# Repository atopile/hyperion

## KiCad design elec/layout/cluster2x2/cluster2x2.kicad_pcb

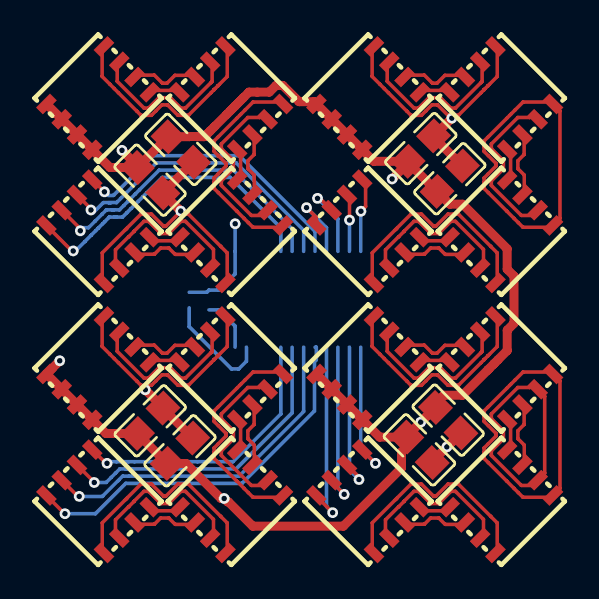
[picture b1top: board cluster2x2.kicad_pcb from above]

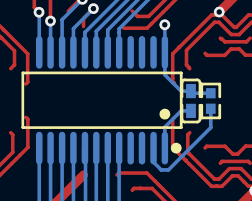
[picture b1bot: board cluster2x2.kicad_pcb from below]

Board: 2 copper layers, 31 parts (3 on the bottom side), 69 nets.

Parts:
C1, C2, C3, C4, C5, C6, C7, C8: 10µF ±10% 25V X5R; C0805
C9: 100nF ±10% 16V X7R; C0402
LED1, LED2, LED3, LED4, LED5, LED6, LED7, LED8, LED9, LED10, LED11, LED12, LED13, LED14, LED15, LED16: LED-SMD_8P-L5.0-W5.0-P1.20_HL-5050RGBW-S1-A27
R1: 309Ω ±1% 62.5mW; R0402
U1: SSOP-24_L8.8-W4.0-P0.64-LS6.2-BL
U2, U3, U4, U5: pixel15

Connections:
REXT: R1.1, U1.23
power-GND: C9.2, R1.2, U1.1
power-VCC: C9.1, U1.24
power_shim-GND: C1.2, C2.2, C3.2, C4.2, C5.2, C6.2, C7.2, C8.2
power_shim-VCC: C1.1, C2.1, C3.1, C4.1, C5.1, C6.1, C7.1, C8.1, LED1.2, LED1.4, LED1.6, LED1.8, LED5.2, LED5.4, LED5.6, LED5.8, LED9.2, LED9.4, LED9.6, LED9.8, LED13.2, LED13.4, LED13.6, LED13.8
rgbs[1]-anodes-anode-0: LED1.3, LED2.4
rgbs[1]-anodes-anode-1: LED1.1, LED2.2
rgbs[1]-anodes-anode-2: LED1.5, LED2.6
rgbs[1]-anodes-anode-3: LED1.7, LED2.8
rgbs[1]-anodes-anode-4: LED5.3, LED6.4
rgbs[1]-anodes-anode-5: LED5.1, LED6.2
rgbs[1]-anodes-anode-6: LED5.5, LED6.6
rgbs[1]-anodes-anode-7: LED5.7, LED6.8
rgbs[1]-anodes-anode-8: LED9.3, LED10.4
rgbs[1]-anodes-anode-9: LED9.1, LED10.2
rgbs[1]-anodes-anode-10: LED9.5, LED10.6
rgbs[1]-anodes-anode-11: LED9.7, LED10.8
rgbs[1]-anodes-anode-12: LED13.3, LED14.4
rgbs[1]-anodes-anode-13: LED13.1, LED14.2
rgbs[1]-anodes-anode-14: LED13.5, LED14.6
rgbs[1]-anodes-anode-15: LED13.7, LED14.8
rgbs[2]-anodes-anode-0: LED2.3, LED3.4
rgbs[2]-anodes-anode-1: LED2.1, LED3.2
rgbs[2]-anodes-anode-2: LED2.5, LED3.6
rgbs[2]-anodes-anode-3: LED2.7, LED3.8
rgbs[2]-anodes-anode-4: LED6.3, LED7.4
rgbs[2]-anodes-anode-5: LED6.1, LED7.2
rgbs[2]-anodes-anode-6: LED6.5, LED7.6
rgbs[2]-anodes-anode-7: LED6.7, LED7.8
rgbs[2]-anodes-anode-8: LED10.3, LED11.4
rgbs[2]-anodes-anode-9: LED10.1, LED11.2
rgbs[2]-anodes-anode-10: LED10.5, LED11.6
rgbs[2]-anodes-anode-11: LED10.7, LED11.8
rgbs[2]-anodes-anode-12: LED14.3, LED15.4
rgbs[2]-anodes-anode-13: LED14.1, LED15.2
rgbs[2]-anodes-anode-14: LED14.5, LED15.6
rgbs[2]-anodes-anode-15: LED14.7, LED15.8
rgbs[3]-anodes-anode-0: LED3.3, LED4.4
rgbs[3]-anodes-anode-1: LED3.1, LED4.2
rgbs[3]-anodes-anode-2: LED3.5, LED4.6
rgbs[3]-anodes-anode-3: LED3.7, LED4.8
rgbs[3]-anodes-anode-4: LED7.3, LED8.4
rgbs[3]-anodes-anode-5: LED7.1, LED8.2
rgbs[3]-anodes-anode-6: LED7.5, LED8.6
rgbs[3]-anodes-anode-7: LED7.7, LED8.8
rgbs[3]-anodes-anode-8: LED11.3, LED12.4
rgbs[3]-anodes-anode-9: LED11.1, LED12.2
rgbs[3]-anodes-anode-10: LED11.5, LED12.6
rgbs[3]-anodes-anode-11: LED11.7, LED12.8
rgbs[3]-anodes-anode-12: LED15.3, LED16.4
rgbs[3]-anodes-anode-13: LED15.1, LED16.2
rgbs[3]-anodes-anode-14: LED15.5, LED16.6
rgbs[3]-anodes-anode-15: LED15.7, LED16.8
rgbs[3]-cathodes-cathode-0: LED4.1, U1.5
rgbs[3]-cathodes-cathode-1: LED16.3, U1.15
rgbs[3]-cathodes-cathode-2: LED16.1, U1.16
rgbs[3]-cathodes-cathode-3: LED12.1, U1.17
rgbs[3]-cathodes-cathode-4: LED12.3, U1.18
rgbs[3]-cathodes-cathode-5: LED12.5, U1.19
rgbs[3]-cathodes-cathode-6: LED12.7, U1.20
rgbs[3]-cathodes-cathode-7: LED4.3, U1.6
rgbs[3]-cathodes-cathode-8: LED4.5, U1.7
rgbs[3]-cathodes-cathode-9: LED4.7, U1.8
rgbs[3]-cathodes-cathode-10: LED8.1, U1.9
rgbs[3]-cathodes-cathode-11: LED8.3, U1.10
rgbs[3]-cathodes-cathode-12: LED8.5, U1.11
rgbs[3]-cathodes-cathode-13: LED8.7, U1.12
rgbs[3]-cathodes-cathode-14: LED16.7, U1.13
rgbs[3]-cathodes-cathode-15: LED16.5, U1.14
